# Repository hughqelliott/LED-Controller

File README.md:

# LED Controller

ATTiny85-based single switch controller for NeoPixels.
Designed and coded for the [Pride LMC](https://hughqelliott.com/blog/pride-lmc/) project.
While the initial code is for a rainbow, the ATTiny85 can run nearly any code for NeoPixels.

### Contributions
   * Initial code and design: [Hugh Elliott](https://hughqelliott.com/blog)
   * PCB design: [Eugene Andruszczenko](https://github.com/EugeneAndruszczenko)

### Versions of code
***
   Auto-divide rainbow *will take any length strip and attempt to divide into 6 equal amounts*

### PCB design
***
   SCH and BRD files available

### STL files for handle
***
   * Main handle
   * Handle bottom
   * Trigger
   * Trigger holder

### Bill of Materials
***
   * 12X12mm Tactile switch
   * M3 Heat Set Inserts
   * M3 screws
   * M5 screws
   * 13X16.8mm Aluminum plywood edging

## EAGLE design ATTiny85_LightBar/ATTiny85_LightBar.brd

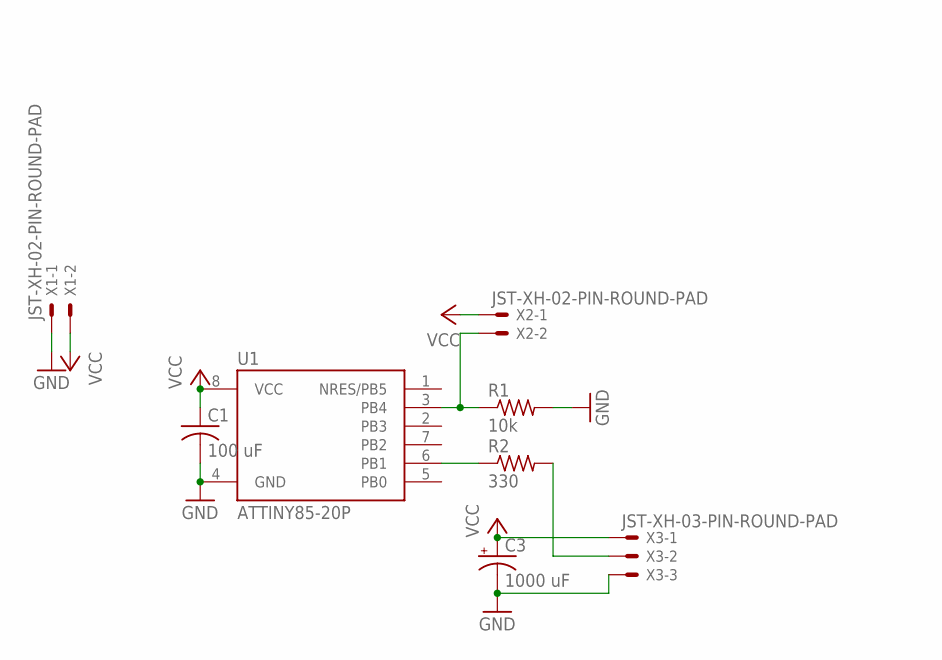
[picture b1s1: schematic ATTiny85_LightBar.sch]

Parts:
C1: 100 uF; C0805
C3: 1000 uF; E5-10,5
R1: 10k; R0805
R2: 330; R0805
U1: ATTINY85-20P; PDIP08_300MIL
X1, X2: JST-XH-02-PIN-ROUND-PAD; JST-XH-02-PACKAGE-ROUND-PAD
X3: JST-XH-03-PIN-ROUND-PAD; JST-XH-03-PACKAGE-ROUND-PAD

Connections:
GND: C1.2, C3.-, R1.2, U1.4 (GND), X1.1, X3.3
unnamed: R1.1, U1.3 (PB4), X2.2
unnamed: R2.1, U1.6 (PB1)
unnamed: R2.2, X3.2
VCC: C1.1, C3.+, U1.8 (VCC), X1.2, X2.1, X3.1

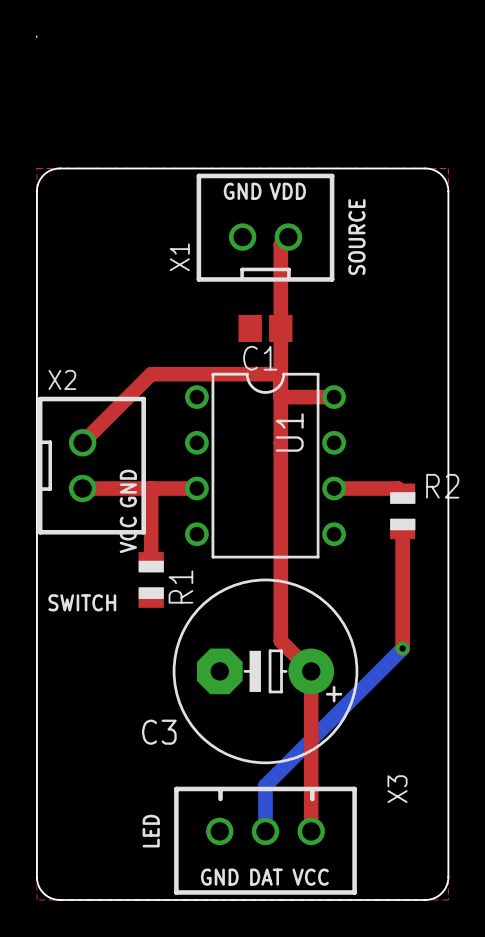
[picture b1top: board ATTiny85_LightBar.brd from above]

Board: 2 copper layers, 22.9 x 47.9 mm, 8 parts (0 on the bottom side), 5 nets.

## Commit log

2021-11-29 updating readme
2021-11-29 autodivide_rainbow code added
2021-11-29 V5 light bar 3D printed parts
2021-11-29 correcting lists in readme
2021-11-29 contributors and horizontal lines
2021-11-29 remove ng in stl list
2021-11-30 additional files for board, cycling code for arduino
2021-11-30 updating corrected files for PCB
2021-12-01 cycle code
2021-12-30 Adding a file for no rainbow. Adding a file for animated transition from colour to colour
2021-12-30 Illustrator file of the basic circuit
2022-04-08 Update autodivide_rainbow.ino
    trying static uint32_t instead of const auto due to an issue uploading recently.
